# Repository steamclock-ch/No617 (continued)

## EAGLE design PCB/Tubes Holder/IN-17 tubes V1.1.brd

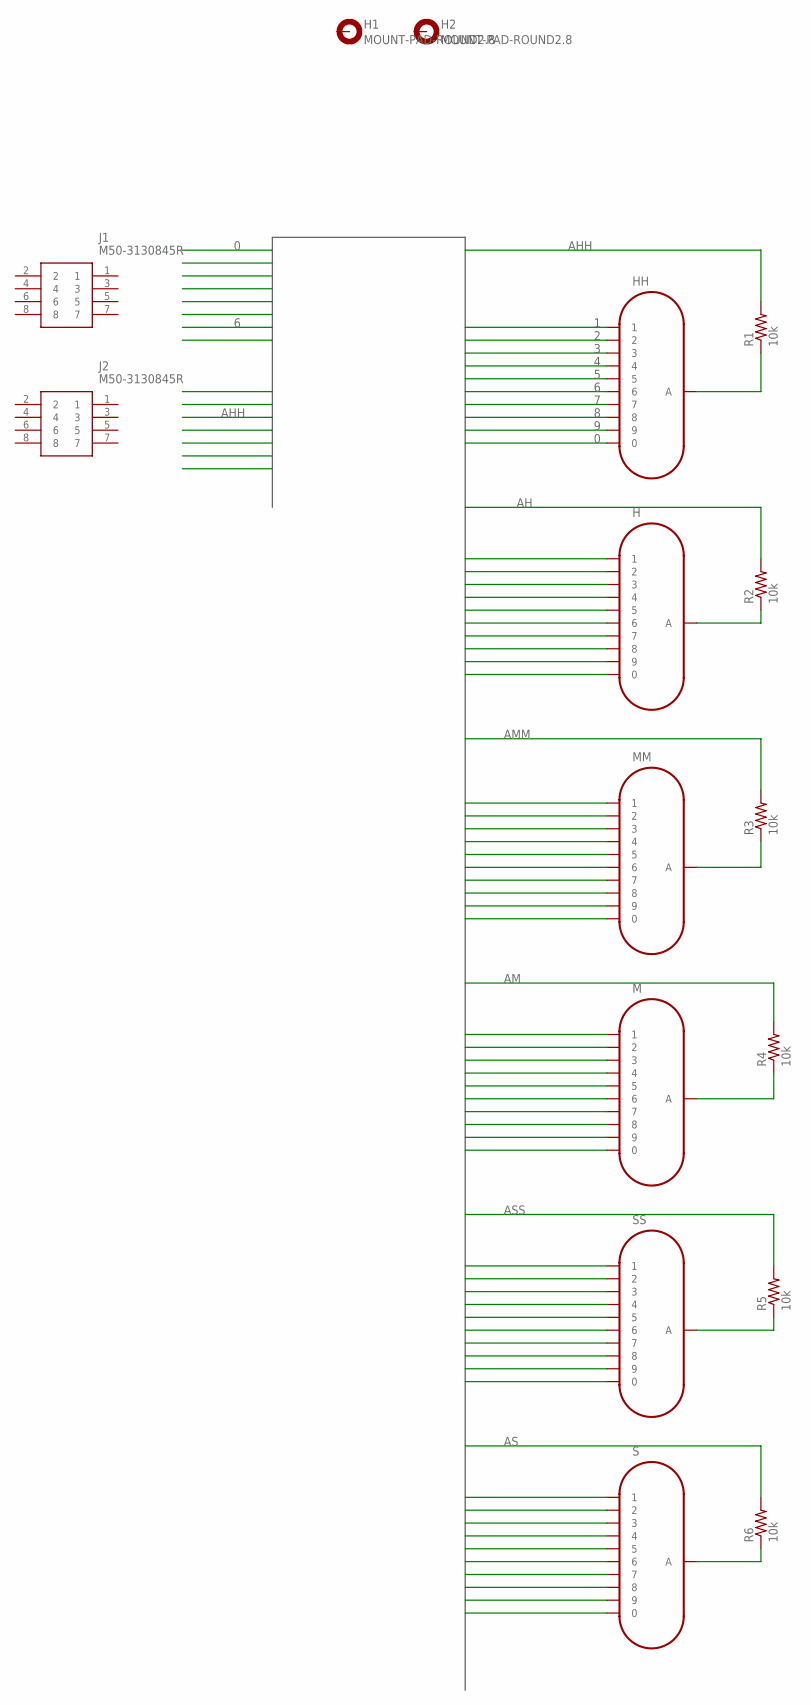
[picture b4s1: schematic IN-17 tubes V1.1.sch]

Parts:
H: IN-17
H1, H2: MOUNT-PAD-ROUND2.8; 2,8-PAD
HH: IN-17
J1, J2: M50-3130845R; M503130845R
M: IN-17
MM: IN-17
R1, R2, R3, R4, R5, R6: 10k; R0805
S: IN-17
SS: IN-17

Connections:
0: H.0, HH.0, M.0, MM.0, S.0, SS.0
1: H.1, HH.1, M.1, MM.1, S.1, SS.1
2: H.2, HH.2, M.2, MM.2, S.2, SS.2
3: H.3, HH.3, M.3, MM.3, S.3, SS.3
4: H.4, HH.4, M.4, MM.4, S.4, SS.4
5: H.5, HH.5, M.5, MM.5, S.5, SS.5
6: H.6, HH.6, M.6, MM.6, S.6, SS.6
7: H.7, HH.7, M.7, MM.7, S.7, SS.7
8: H.8, HH.8, M.8, MM.8, S.8, SS.8
9: H.9, HH.9, M.9, MM.9, S.9, SS.9
AH: R2.2
AHH: R1.2
AM: R4.2
AMM: R3.2
AS: R6.2
ASS: R5.2
unnamed: HH.A, R1.1
unnamed: R6.1, S.A
unnamed: R5.1, SS.A
unnamed: M.A, R4.1
unnamed: MM.A, R3.1
unnamed: H.A, R2.1

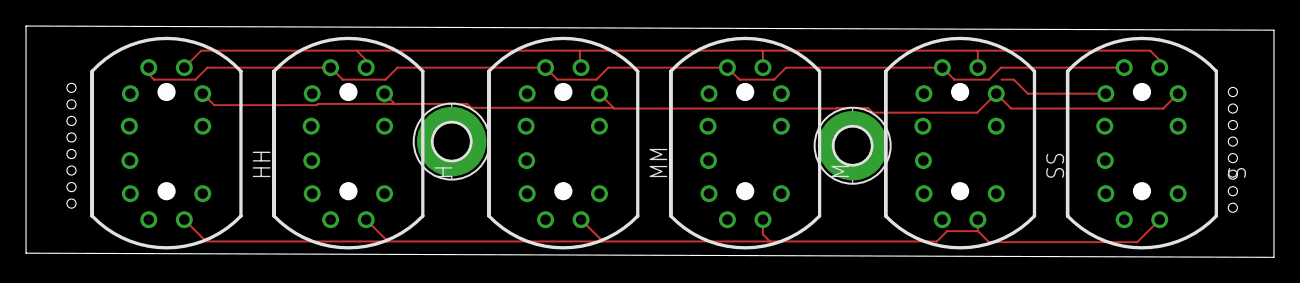
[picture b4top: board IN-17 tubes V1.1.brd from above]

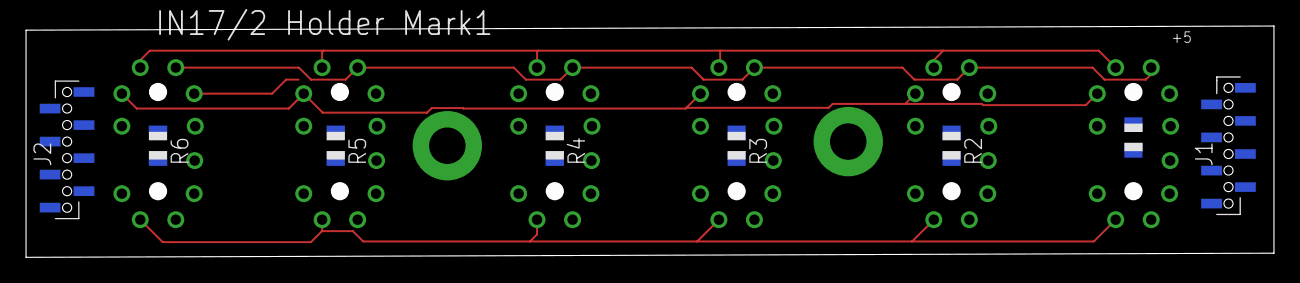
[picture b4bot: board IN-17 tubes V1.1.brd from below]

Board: 2 copper layers, 95.9 x 17.8 mm, 16 parts (8 on the bottom side), 16 nets.

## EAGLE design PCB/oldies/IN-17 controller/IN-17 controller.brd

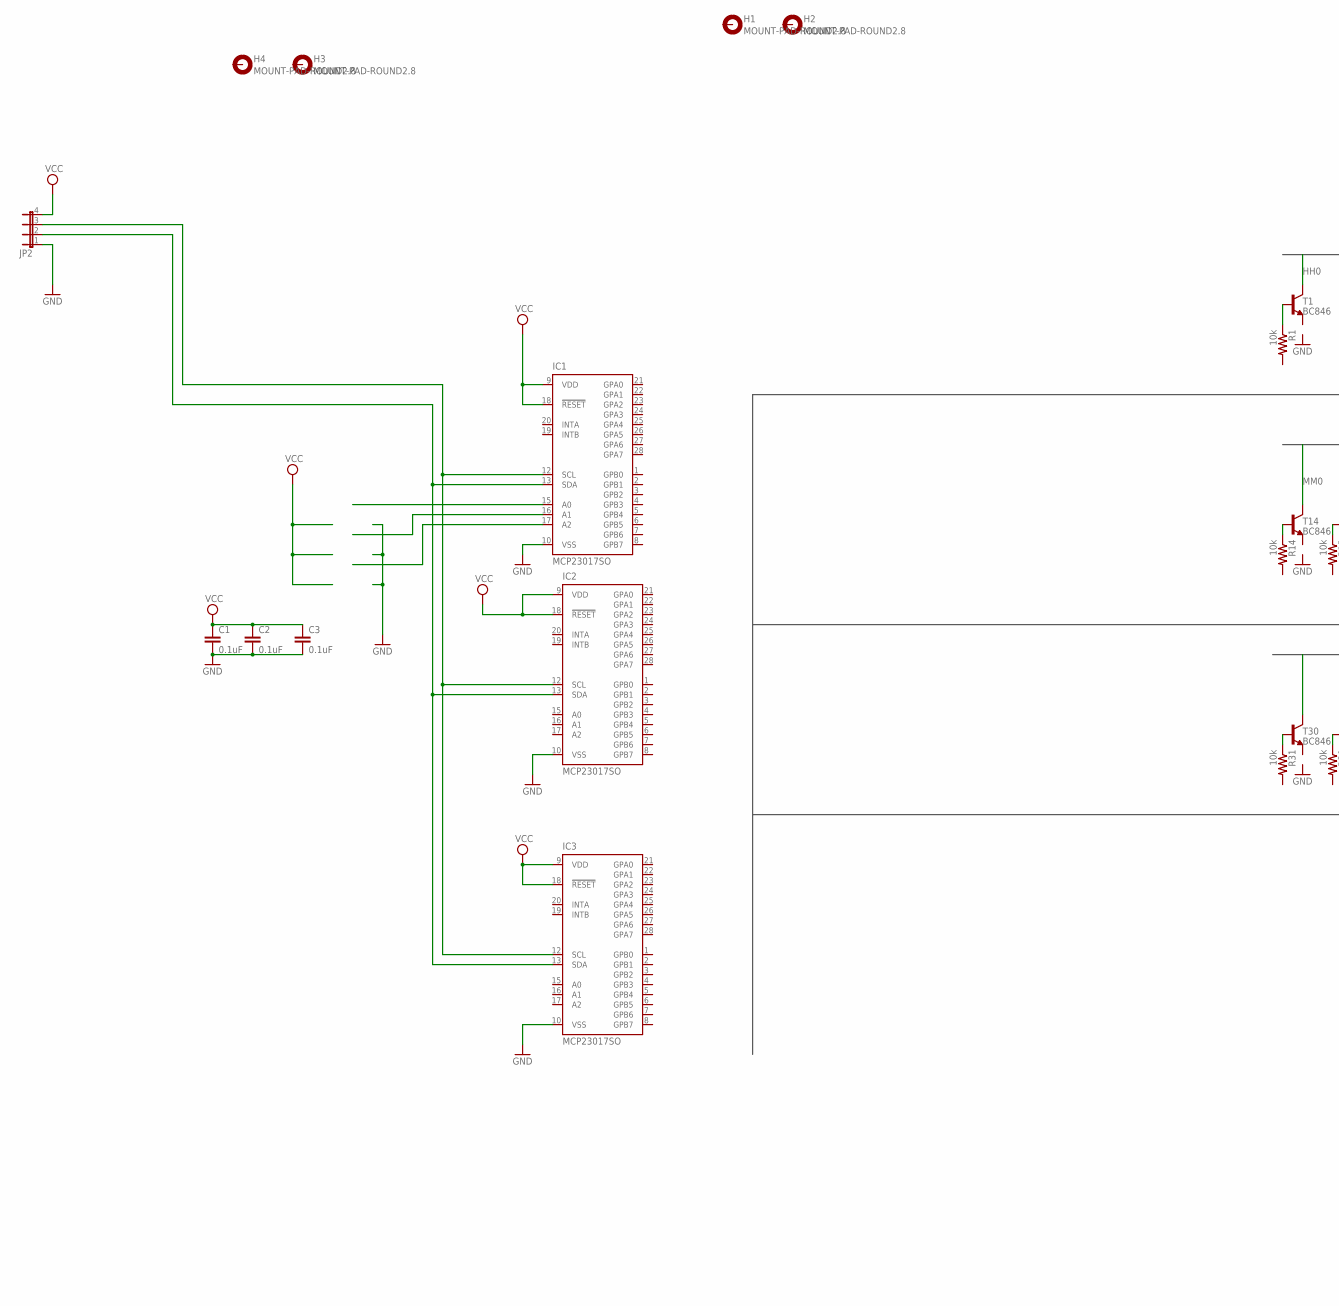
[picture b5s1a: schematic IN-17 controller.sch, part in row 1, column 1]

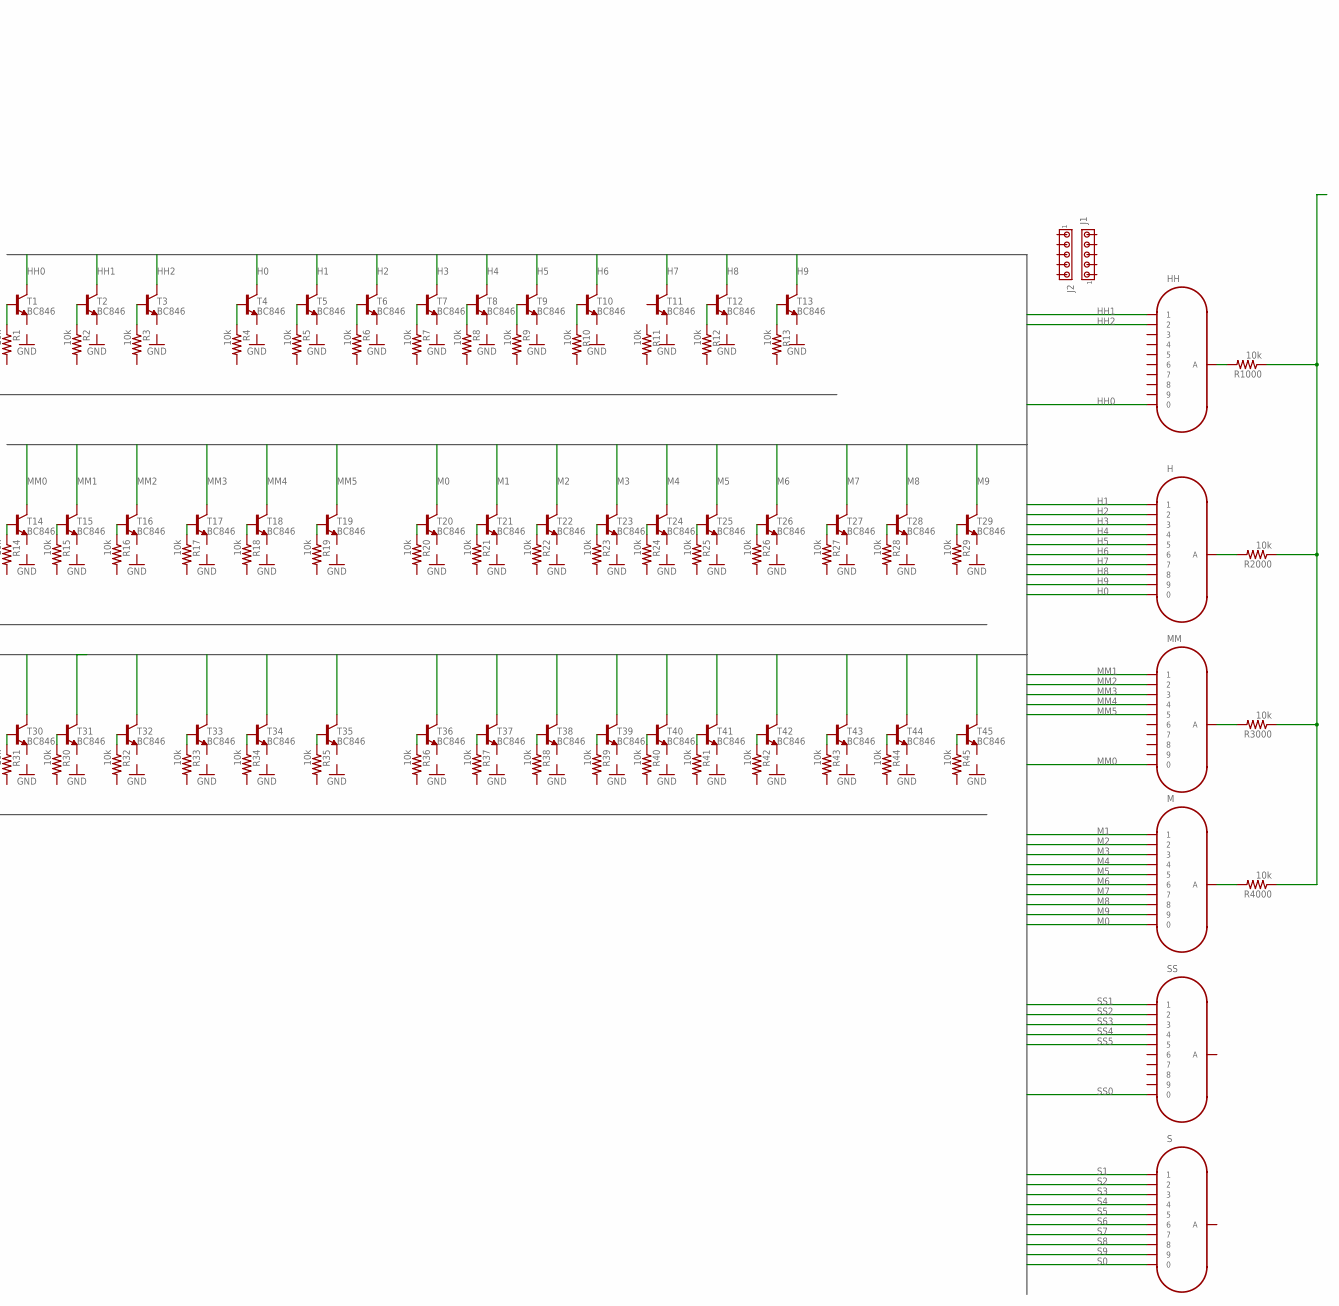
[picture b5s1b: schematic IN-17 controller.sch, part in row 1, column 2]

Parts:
C1, C2, C3: 0.1uF; C1206
H: IN-17
H1, H2, H3, H4: MOUNT-PAD-ROUND2.8; 2,8-PAD
HH: IN-17
IC1, IC2, IC3: MCP23017SO; SO28W
J1, J2: MTA05-100; 10X05MTA
JP2: JP4E; JP4
M: IN-17
MM: IN-17
R1, R2, R3, R4, R5, R6, R7, R8, R9, R10, R11, R12, R13, R14, R15, R16, R17, R18, R19, R20, R21, R22, R23, R24, R25, R26, R27, R28, R29, R30, R31, R32, R33, R34, R35, R36, R37, R38, R39, R40, R41, R42, R43, R44, R45, R1000, R2000, R3000, R4000: 10k; M0805
S: IN-17
SS: IN-17
T1, T2, T3, T4, T5, T6, T7, T8, T9, T10, T11, T12, T13, T14, T15, T16, T17, T18, T19, T20, T21, T22, T23, T24, T25, T26, T27, T28, T29, T30, T31, T32, T33, T34, T35, T36, T37, T38, T39, T40, T41, T42, T43, T44, T45: BC846; SOT23

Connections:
GND: C1.2, C2.2, C3.2, IC1.10 (VSS), IC2.10 (VSS), IC3.10 (VSS), JP2.1
H0: H.0, T4.3 (C)
H1: H.1, T5.3 (C)
H2: H.2, T6.3 (C)
H3: H.3, T7.3 (C)
H4: H.4, T8.3 (C)
H5: H.5, T9.3 (C)
H6: H.6, T10.3 (C)
H7: H.7, T11.3 (C)
H8: H.8, T12.3 (C)
H9: H.9, T13.3 (C)
HH0: HH.0, T1.3 (C)
HH1: HH.1, T2.3 (C)
HH2: HH.2, T3.3 (C)
M0: M.0, T20.3 (C)
M1: M.1, T21.3 (C)
M2: M.2, T22.3 (C)
M3: M.3, T23.3 (C)
M4: M.4, T24.3 (C)
M5: M.5, T25.3 (C)
M6: M.6, T26.3 (C)
M7: M.7, T27.3 (C)
M8: M.8, T28.3 (C)
M9: M.9, T29.3 (C)
MM0: MM.0, T14.3 (C)
MM1: MM.1, T15.3 (C)
MM2: MM.2, T16.3 (C)
MM3: MM.3, T17.3 (C)
MM4: MM.4, T18.3 (C)
MM5: MM.5, T19.3 (C)
unnamed: R4.1, T4.1 (B)
unnamed: R14.1, T14.1 (B)
unnamed: R5.1, T5.1 (B)
unnamed: R6.1, T6.1 (B)
unnamed: R1.1, T1.1 (B)
unnamed: R2.1, T2.1 (B)
unnamed: R3.1, T3.1 (B)
unnamed: M.A, R4000.2
unnamed: R7.1, T7.1 (B)
unnamed: R8.1, T8.1 (B)
unnamed: R9.1, T9.1 (B)
unnamed: R10.1, T10.1 (B)
unnamed: H.A, R2000.2
unnamed: R12.1, T12.1 (B)
unnamed: R13.1, T13.1 (B)
unnamed: MM.A, R3000.2
unnamed: R15.1, T15.1 (B)
unnamed: R16.1, T16.1 (B)
unnamed: R17.1, T17.1 (B)
unnamed: R18.1, T18.1 (B)
unnamed: R19.1, T19.1 (B)
unnamed: R20.1, T20.1 (B)
unnamed: R21.1, T21.1 (B)
unnamed: R22.1, T22.1 (B)
unnamed: R23.1, T23.1 (B)
unnamed: R24.1, T24.1 (B)
unnamed: R25.1, T25.1 (B)
unnamed: R26.1, T26.1 (B)
unnamed: R27.1, T27.1 (B)
unnamed: R28.1, T28.1 (B)
unnamed: R29.1, T29.1 (B)
unnamed: R31.1, T30.1 (B)
unnamed: R30.1, T31.1 (B)
unnamed: R32.1, T32.1 (B)
unnamed: R1000.1, R2000.1, R3000.1, R4000.1
unnamed: R33.1, T33.1 (B)
unnamed: R34.1, T34.1 (B)
unnamed: R35.1, T35.1 (B)
unnamed: R36.1, T36.1 (B)
unnamed: R37.1, T37.1 (B)
unnamed: R38.1, T38.1 (B)
unnamed: R39.1, T39.1 (B)
unnamed: R40.1, T40.1 (B)
unnamed: HH.A, R1000.2
unnamed: R41.1, T41.1 (B)
unnamed: R42.1, T42.1 (B)
unnamed: R44.1, T44.1 (B)
unnamed: R45.1, T45.1 (B)
unnamed: R43.1, T43.1 (B)
unnamed: IC1.13 (SDA), IC2.13 (SDA), IC3.13 (SDA), JP2.2
unnamed: IC1.12 (SCL), IC2.12 (SCL), IC3.12 (SCL), JP2.3
S0: S.0, T36.3 (C)
S1: S.1, T37.3 (C)
S2: S.2, T38.3 (C)
S3: S.3, T39.3 (C)
S4: S.4, T40.3 (C)
S5: S.5, T41.3 (C)
S6: S.6, T42.3 (C)
S7: S.7, T43.3 (C)
S8: S.8, T44.3 (C)
S9: S.9, T45.3 (C)
SS0: SS.0, T30.3 (C)
SS1: SS.1, T31.3 (C)
SS2: SS.2, T32.3 (C)
SS3: SS.3, T33.3 (C)
SS4: SS.4, T34.3 (C)
SS5: SS.5, T35.3 (C)
VCC: C1.1, C2.1, C3.1, IC1.9 (VDD), IC1.18 (!RESET), IC2.9 (VDD), IC2.18 (!RESET), IC3.9 (VDD), IC3.18 (!RESET)

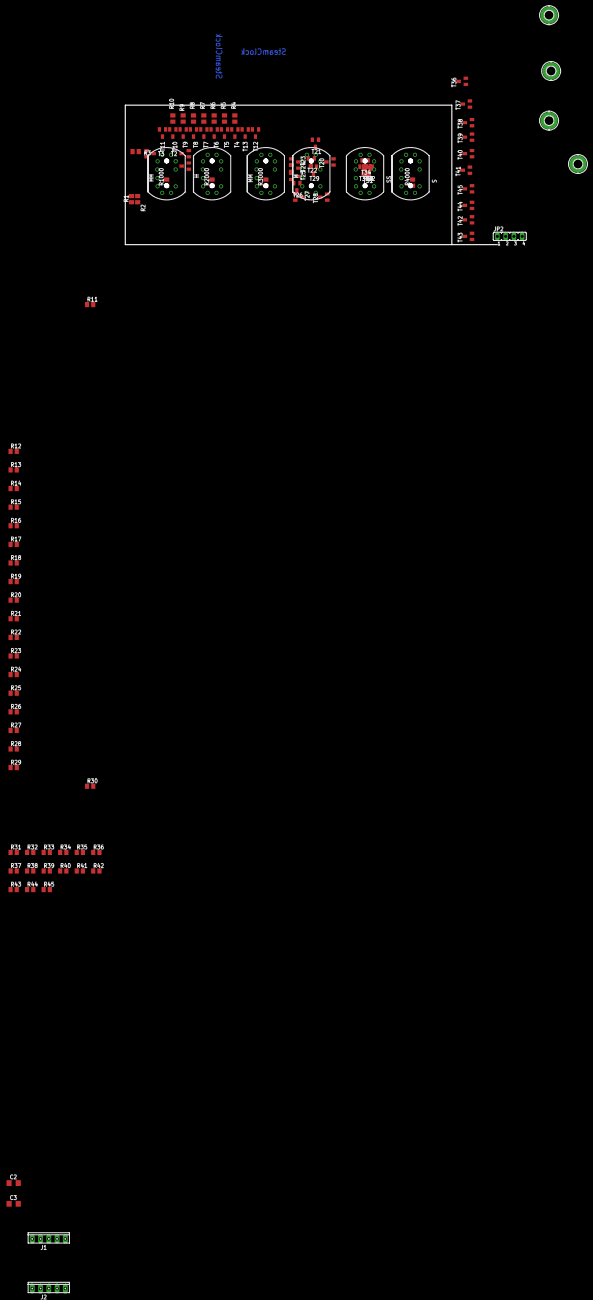
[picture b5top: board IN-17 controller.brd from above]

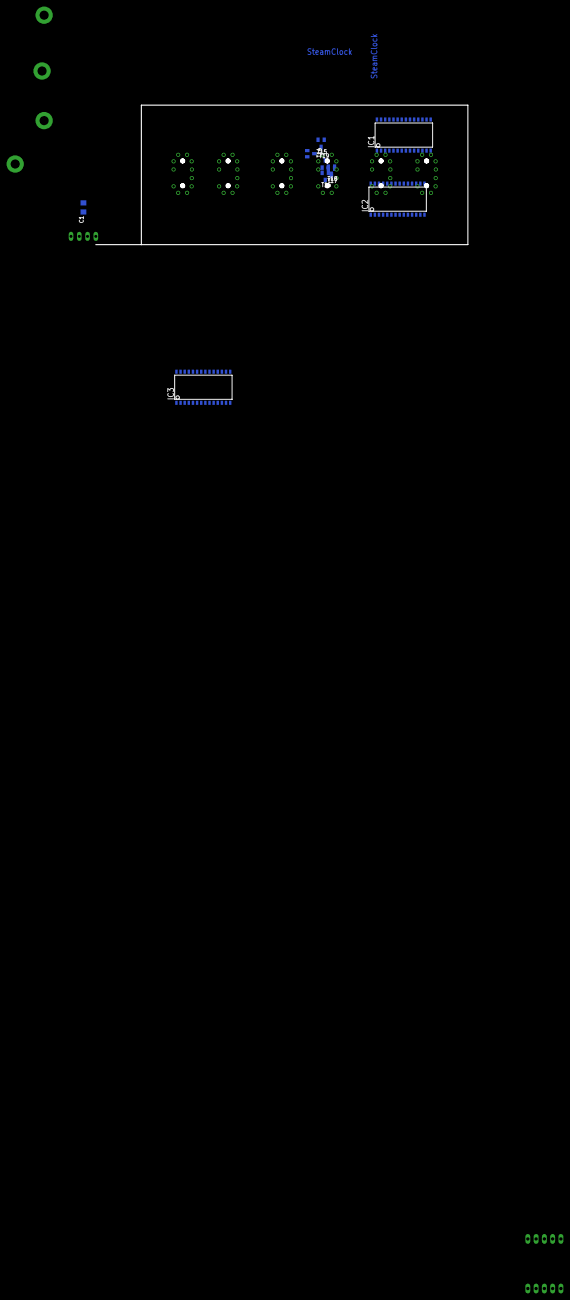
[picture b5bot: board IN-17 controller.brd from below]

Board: 2 copper layers, 114.3 x 42.9 mm, 113 parts (10 on the bottom side), 98 nets.

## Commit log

2022-07-02 init
